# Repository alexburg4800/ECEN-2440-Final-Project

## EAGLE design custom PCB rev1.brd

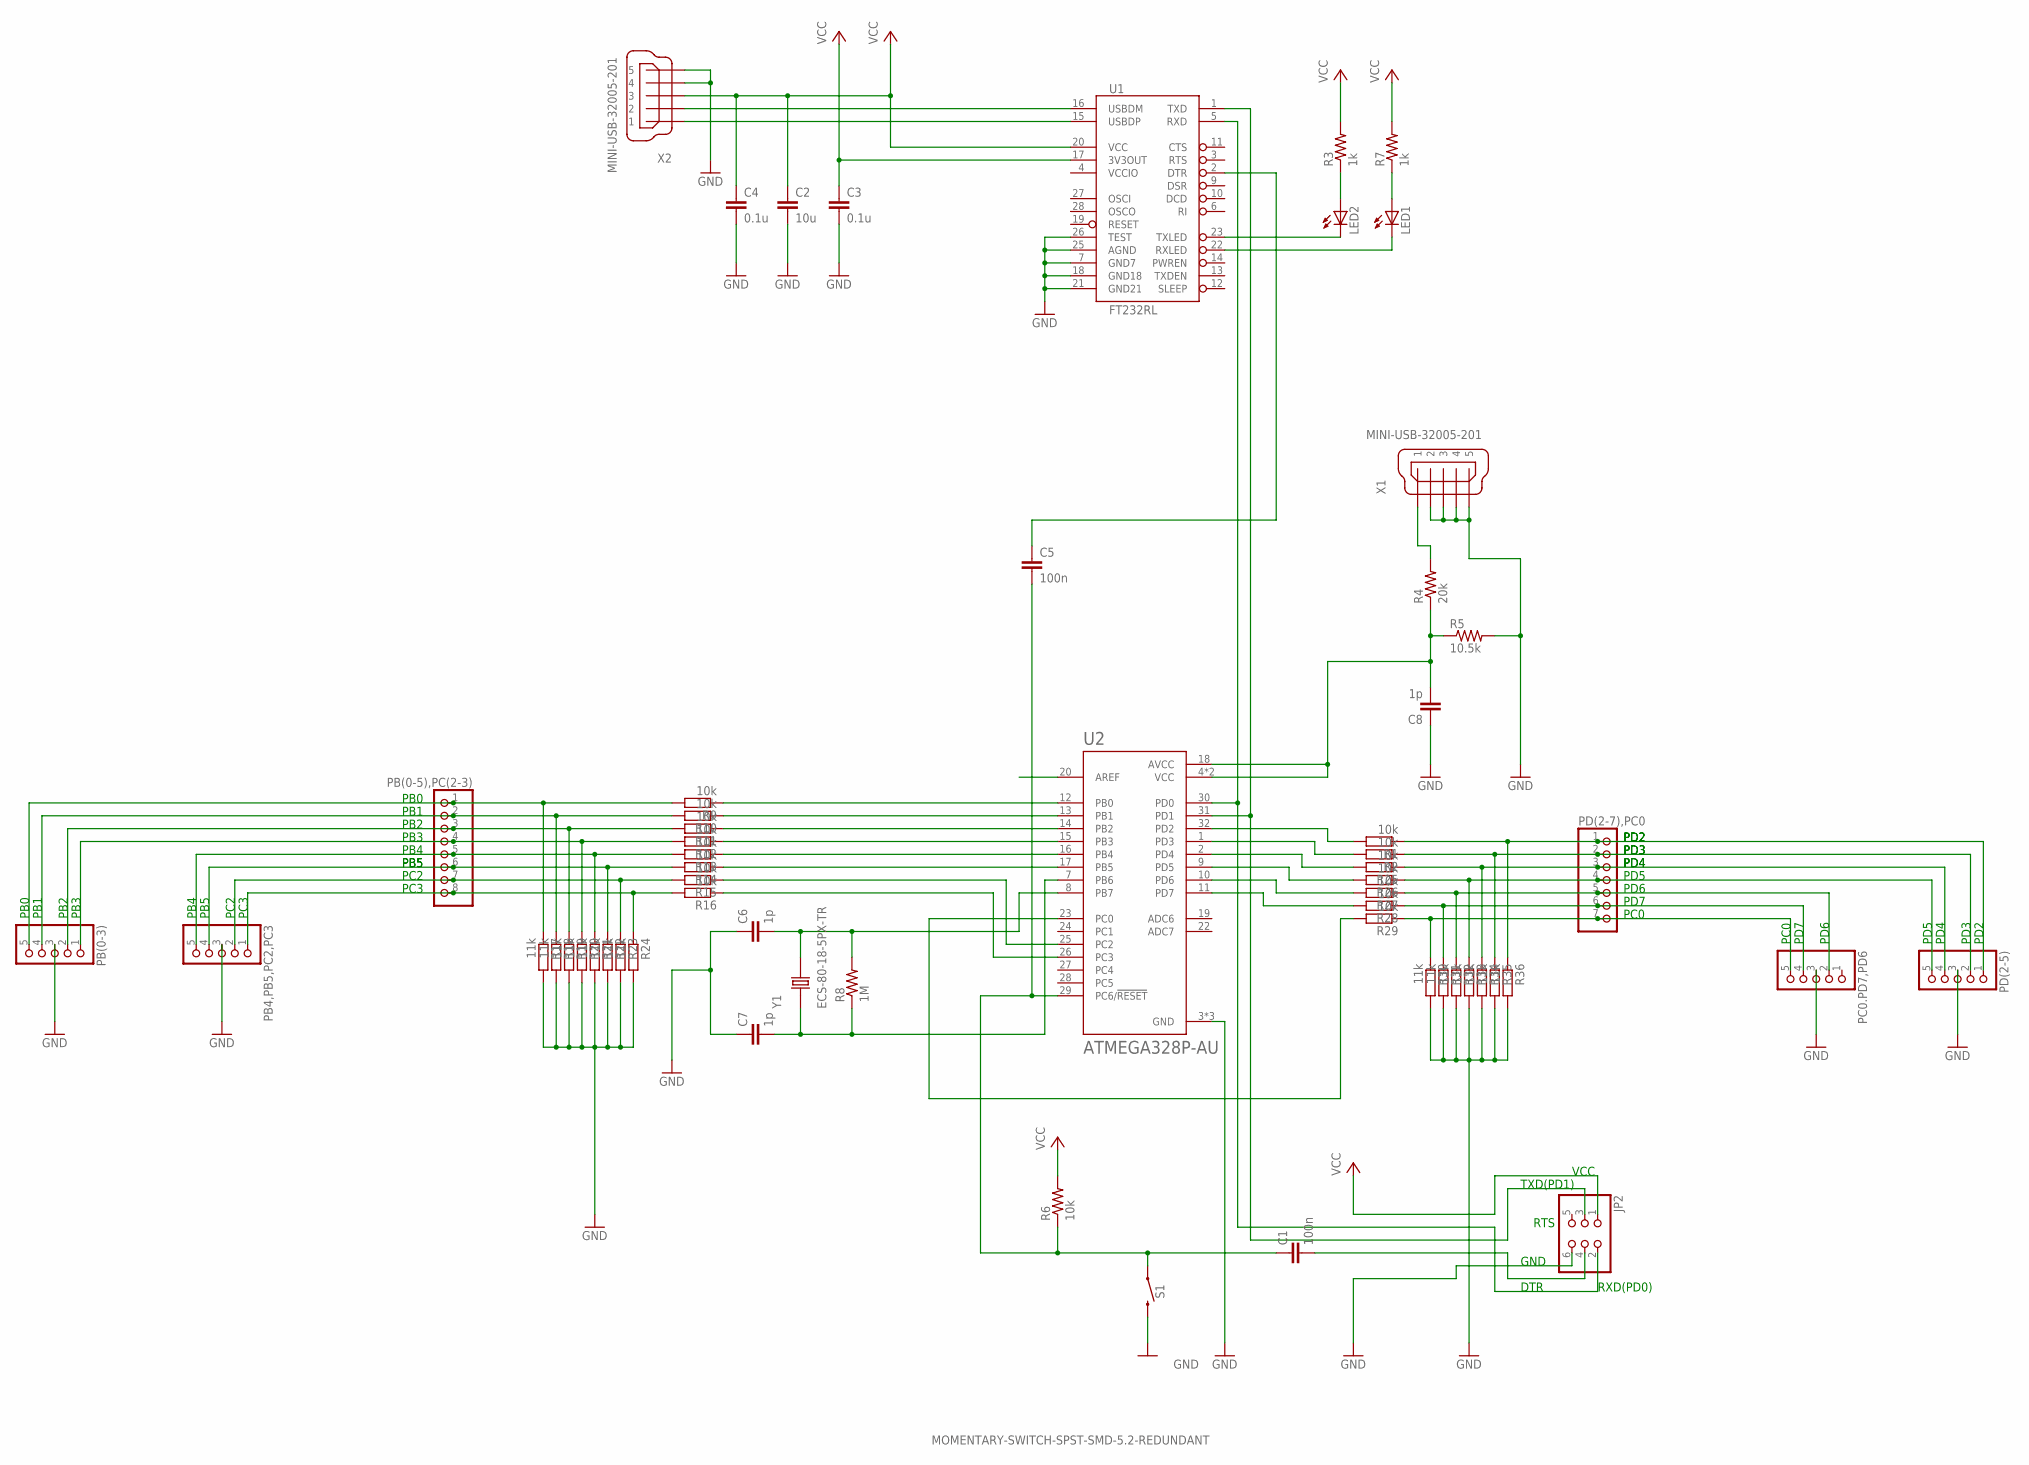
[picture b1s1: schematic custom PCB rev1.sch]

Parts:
C1, C5: 100n; C0603K
C2: 10u; C0603K
C3, C4: 0.1u; C0603K
C6, C7, C8: 1p; C0603K
JP2: PINHD-2X3; 2X03
LED1, LED2: LEDCHIP-LED0603; CHIP-LED0603
PB4,PB5,PC2,PC3: PINHD-1X5; 1X05
PB(0-3): PINHD-1X5; 1X05
PB(0-5),PC(2-3): PINHD-1X8; 1X08
PC0.PD7,PD6: PINHD-1X5; 1X05
PD(2-5): PINHD-1X5; 1X05
PD(2-7),PC0: PINHD-1X7; 1X07
R1, R2, R9, R10, R11, R12, R13, R14, R15, R16, R25, R26, R27, R28, R29: 10k; R0402
R3, R7: 1k; R0603
R4: 20k; R0603
R5: 10.5k; R0603
R6: 10k; R0603
R8: 1M; R0603
R17, R18, R19, R20, R21, R22, R23, R24, R30, R31, R32, R33, R34, R35, R36: 11k; R0402
S1: MOMENTARY-SWITCH-SPST-SMD-5.2-REDUNDANT; TACTILE_SWITCH_SMD_5.2MM
U1: FT232RL; SSOP28DB
U2: ATMEGA328P-AU; QFP80P900X900X120-32N
X1, X2: MINI-USB-32005-201; 32005-201
Y1: ECS-80-18-5PX-TR; XTAL_ECS-80-18-5PX-TR

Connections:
GND: C2.2, C3.2, C4.2, C8.1, JP2.6, PB4,PB5,PC2,PC3.3, PB(0-3).3, PC0.PD7,PD6.3, PD(2-5).3, R30.2, R31.2, R32.2, R33.2, R34.2, R35.2, R36.2, S1.3 (2), S1.4 (2), U1.7 (GND7), U1.18 (GND18), U1.21 (GND21), U1.25 (AGND), U1.26 (TEST), U2.3 (GND), U2.5 (GND), U2.21 (GND), X2.4, X2.5
unnamed: R9.1, U2.12 (PB0)
unnamed: R10.1, U2.13 (PB1)
unnamed: R11.1, U2.14 (PB2)
unnamed: R12.1, U2.15 (PB3)
unnamed: R13.1, U2.16 (PB4)
unnamed: R14.1, U2.17 (PB5)
unnamed: R15.1, U2.25 (PC2)
unnamed: R16.1, U2.26 (PC3)
unnamed: PB(0-3).5, PB(0-5),PC(2-3).1, R9.2, R17.1
unnamed: PB(0-3).4, PB(0-5),PC(2-3).2, R10.2, R18.1
unnamed: PB(0-3).2, PB(0-5),PC(2-3).3, R11.2, R19.1
unnamed: PB(0-3).1, PB(0-5),PC(2-3).4, R12.2, R20.1
unnamed: PB4,PB5,PC2,PC3.5, PB(0-5),PC(2-3).5, R13.2, R21.1
unnamed: PB4,PB5,PC2,PC3.4, PB(0-5),PC(2-3).6, R14.2, R22.1
unnamed: PB4,PB5,PC2,PC3.2, PB(0-5),PC(2-3).7, R15.2, R23.1
unnamed: PB4,PB5,PC2,PC3.1, PB(0-5),PC(2-3).8, R16.2, R24.1
unnamed: R1.2, U2.32 (PD2)
unnamed: R2.2, U2.1 (PD3)
unnamed: R25.2, U2.2 (PD4)
unnamed: R26.2, U2.9 (PD5)
unnamed: R27.2, U2.10 (PD6)
unnamed: R28.2, U2.11 (PD7)
unnamed: R29.2, U2.23 (PC0)
unnamed: PC0.PD7,PD6.5, PD(2-7),PC0.7, R29.1, R30.1
unnamed: PC0.PD7,PD6.4, PD(2-7),PC0.6, R28.1, R31.1
unnamed: PC0.PD7,PD6.2, PD(2-7),PC0.5, R27.1, R32.1
unnamed: PD(2-5).5, PD(2-7),PC0.4, R26.1, R33.1
unnamed: PD(2-5).4, PD(2-7),PC0.3, R25.1, R34.1
unnamed: PD(2-5).2, PD(2-7),PC0.2, R2.1, R35.1
unnamed: PD(2-5).1, PD(2-7),PC0.1, R1.1, R36.1
unnamed: C1.2, JP2.4
unnamed: JP2.3, U1.1 (TXD), U2.31 (PD1)
unnamed: C1.1, C5.2, R6.1, S1.1, S1.2 (1), U2.29 (PC6/!RESET)
unnamed: C8.2, R4.1, R5.1, U2.4 (VCC), U2.6 (VCC), U2.18 (AVCC)
unnamed: R5.2, X1.2, X1.3, X1.4, X1.5
unnamed: U1.15 (USBDP), X2.1
unnamed: U1.16 (USBDM), X2.2
unnamed: LED2.A, R3.1
unnamed: LED1.A, R7.1
unnamed: LED2.C, U1.23 (TXLED)
unnamed: LED1.C, U1.22 (RXLED)
unnamed: C6.2, R8.2, U2.8 (PB7), Y1.2
unnamed: C7.2, R8.1, U2.7 (PB6), Y1.1
unnamed: C5.1, U1.2 (DTR)
unnamed: C6.1, C7.1
unnamed: R17.2, R18.2, R19.2, R20.2, R21.2, R22.2, R23.2, R24.2
unnamed: R4.2, X1.1
unnamed: JP2.2, U1.5 (RXD), U2.30 (PD0)
VCC: C2.1, C3.1, C4.1, JP2.1, R3.2, R6.2, R7.2, U1.17 (3V3OUT), U1.20 (VCC), X2.3
VCCIO: U1.4 (VCCIO)

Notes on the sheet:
VCC
RXD(PD0)
TXD(PD1)
DTR
RTS
GND
PD2
PD3
PD4
PD5
PD6
PD7
PC0
PB0
PB1
PB2
PB3
PB4
PB5
PC2
PC3

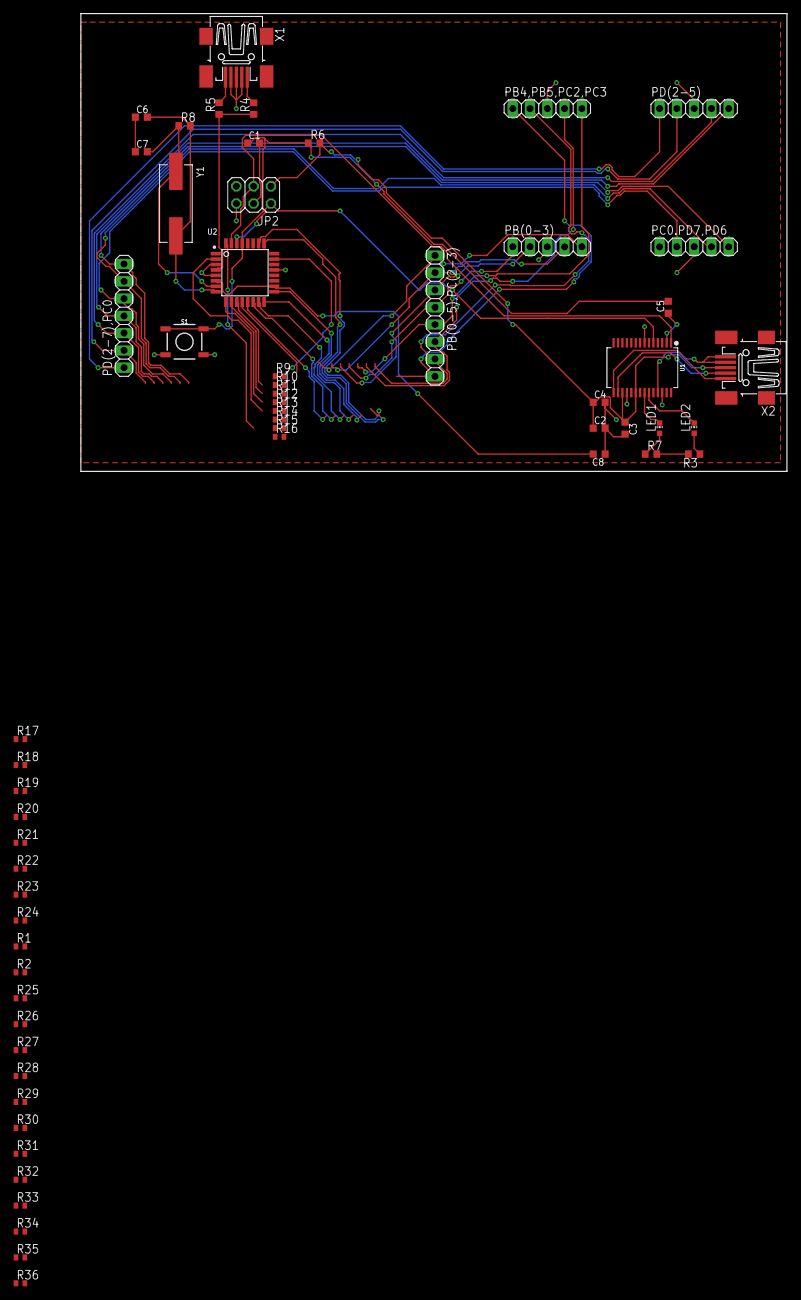
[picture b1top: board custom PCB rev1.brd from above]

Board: 2 copper layers, 103.8 x 67.3 mm, 59 parts (0 on the bottom side), 50 nets.

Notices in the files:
parts and their libraries:
SparkFun-Switches: Licensing: Creative Commons ShareAlike 4.0 International - https://creativecommons.org/licenses/by-sa/4.0
